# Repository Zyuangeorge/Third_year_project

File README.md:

# Third_year_project
This a python-based GUI, which is used for a battery management system project

## Hardware Requirement
1. S32K144EVB-used for serial communication

2. MC33771C BCC chip-used for battery data monitoring

3. BATT-14 emulator-used for emulating the 14 battery cells

## Software Requirement
1. Python V3.10

2. Python library

 * pyqtgraph     - data plotting

 * pandas        - data outputting

 * numpy         - data plotting

 * PySide6       - GUI building

 * PySerial        - serial communication
 
 * Plotly        - data plotting
 
## Main features
1. Serial communication with configuration of serial port

2. Real time data recording and output in .csv

3. Threshold values setting

4. Battery cell voltage displaying

5. Battery pack voltage and current displaying

6. Battery control IC temperature displaying

7. Battery and IC status displaying

8. Battery data plotting

9. CSV data opening

10. Curve zooming

11. Battery SOC and SOH information display

12. Data plotting

13. Cell balancing control

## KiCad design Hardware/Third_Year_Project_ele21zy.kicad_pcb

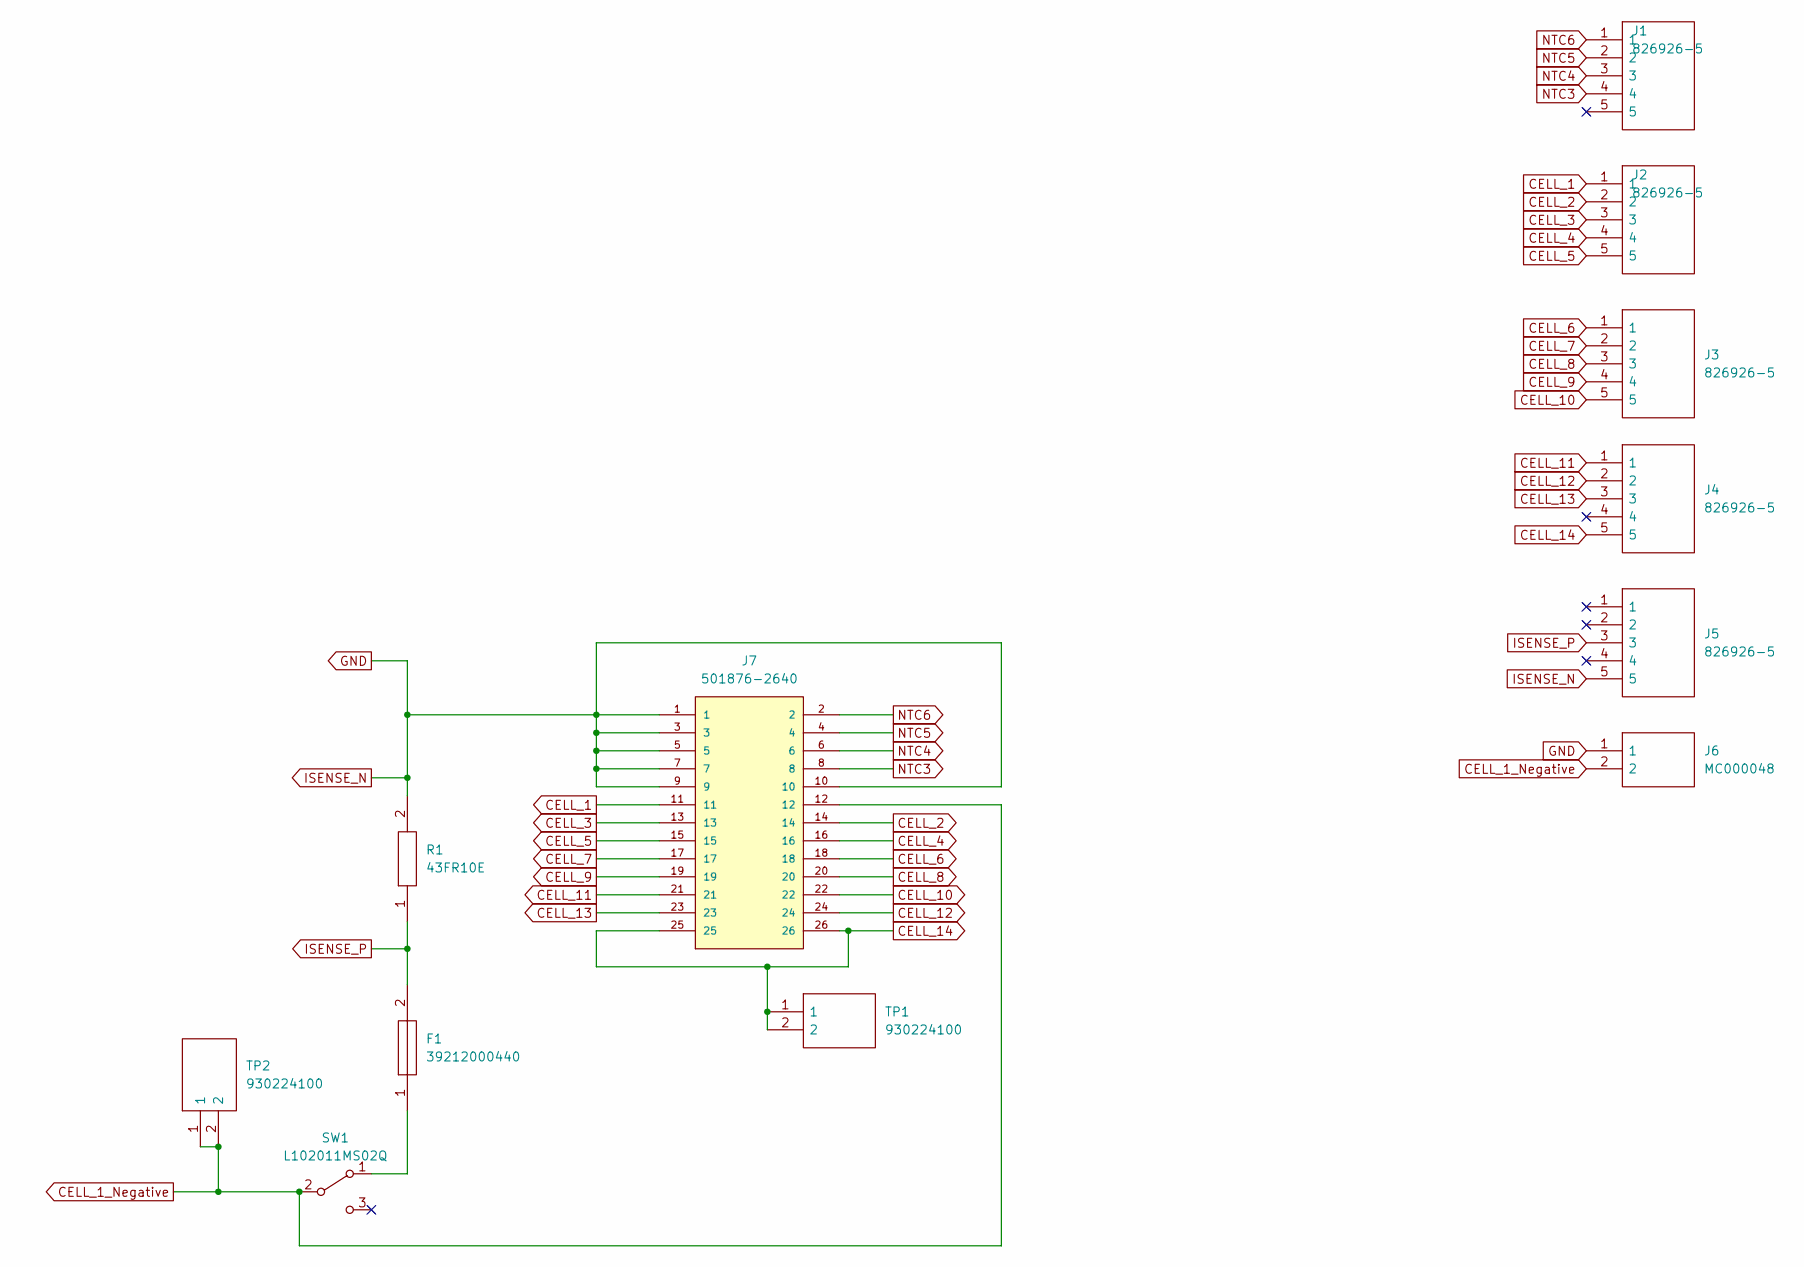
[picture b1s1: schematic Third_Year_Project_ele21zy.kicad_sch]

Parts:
F1: 39212000440; 39213150440_1; Manufacturer_Part_Number 39212000440
J1, J2, J3, J4, J5: 826926-5; RHDR5W74P0X254_1X5_1320X250X850P; Manufacturer_Part_Number 2212S-05SG-85
J6: MC000048; Manufacturer_Part_Number MC000048
J7: 501876-2640; MOLEX_501876-2640; PARTREV D
R1: 43FR10E; RESAD3750W90L1510D560; Manufacturer_Part_Number 43FR10E
SW1: L102011MS02Q
TP1, TP2: 930224100; Manufacturer_Part_Number 930224100

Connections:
CELL_1: J2.1, J7.11
CELL_1_Negative: J6.2, J7.12, SW1.2 (B), TP2.1, TP2.2
CELL_2: J2.2, J7.14
CELL_3: J2.3, J7.13
CELL_4: J2.4, J7.16
CELL_5: J2.5, J7.15
CELL_6: J3.1, J7.18
CELL_7: J3.2, J7.17
CELL_8: J3.3, J7.20
CELL_9: J3.4, J7.19
CELL_10: J3.5, J7.22
CELL_11: J4.1, J7.21
CELL_12: J4.2, J7.24
CELL_13: J4.3, J7.23
CELL_14: J4.5, J7.25, J7.26, TP1.1, TP1.2
GND: J5.5, J6.1, J7.1, J7.3, J7.5, J7.7, J7.9, J7.10, R1.2
ISENSE_P: F1.2, J5.3, R1.1
NTC3: J1.4, J7.8
NTC4: J1.3, J7.6
NTC5: J1.2, J7.4
NTC6: J1.1, J7.2
unnamed: F1.1, SW1.1 (A)

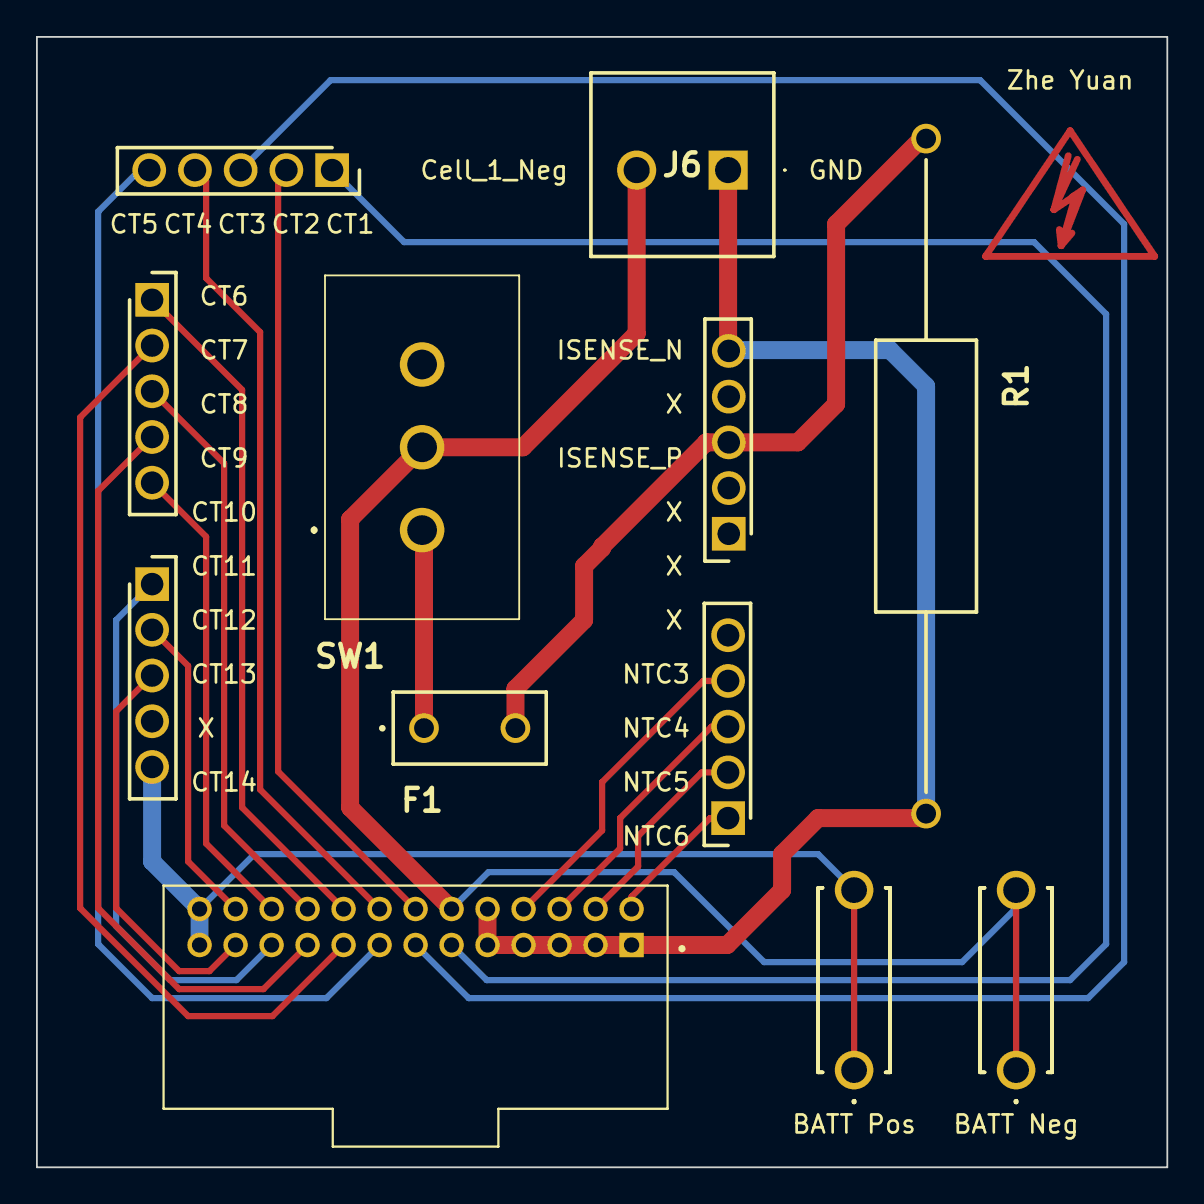
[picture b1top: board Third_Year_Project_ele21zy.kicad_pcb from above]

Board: 2 copper layers, 62.8 x 62.8 mm, 12 parts (0 on the bottom side), 22 nets.

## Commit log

2022-10-28 update GUI
2022-10-28 convert GUI to .py
2022-10-28 update UI display
2022-10-28 fix battery data display
2022-10-29 update data init
2022-10-29 update start monitor and stop monitor
2022-10-29 update util
2022-10-29 update battery status display
2022-10-29 cell status update
2022-10-29 update status button
2022-10-29 update pack status
2022-10-29 update com
2022-10-29 update receivedata
2022-10-30 update comment
2022-11-02 update UART transfer
2022-11-02 update status display
2022-11-03 update S32K codes
2022-11-06 update GUI UART transmission finished
2022-11-06 update folder structure
2022-11-06 update BMS_V1 finished
2022-11-06 update src file
2022-11-06 update version comment
2022-11-07 update GUI bugs' fixes
2022-11-07 update ui to graph button
2022-11-07 update graph demo
2022-11-07 update plot graph
2022-11-09 update graph plotting
2022-11-09 remove graph buttons
2022-11-09 update small changes
2022-11-09 update recording function(no output)
2022-11-09 update csv output
2022-11-09 update logo
2022-11-09 update small bugs
2022-11-10 update zoom graph
2022-11-10 update load data
2022-11-10 update plot window
2022-11-11 update open file
2022-11-13 update import format
2022-11-22 update current measurement
2022-11-22 update s32k code
2022-11-26 update cc method
2022-11-26 update S32K main
2022-11-28 update S32K V3 Enhanced CC
2022-11-28 update SoC and SoH (high memory)
2022-11-29 update minus value receiving
2022-11-30 Fix bugs of SoC and SoH estimation
2022-11-30 BMS GUI Version 7.3 Features: *Update automatic data output
2022-12-01 BMS GUI Version 8 Features: *Update loading data
2022-12-01 update x axis values
2022-12-01 BMS GUI Version 8.1 Features: *Update auto axis
2022-12-01 BMS GUI Version 8.2 Features: *Update EFC measurement
2022-12-01 update minus current
2022-12-02 update GUI (no focus)
2022-12-02 update exporting bugs
2022-12-02 update S32K LED, gc collect
2022-12-02 update threshold
2022-12-05 update s32K fault state
2022-12-05 Update main.c
    update threshold margin
2022-12-06 update format
2022-12-06 fix port status bug
2022-12-06 fix clear data
2022-12-06 update output directory
2022-12-10 update plotly
2022-12-10 update auto output
2022-12-11 update plotly function
2022-12-12 update OCV plot
2022-12-12 update git ignore
2022-12-12 update data
2022-12-12 update auto plotting
2022-12-12 update memory usage
2022-12-13 fix plot bugs
2022-12-13 change output time 60 to 3600
2022-12-15 update stop monitor when the port is disconnected
2022-12-15 update import plotly
2022-12-16 update OcvPlot Unit
2022-12-16 update unit test
2022-12-23 update version information and add sitation file
2022-12-23 update cff
2022-12-23 update test
2022-12-23 updata data
2022-12-30 update comment and data
2022-12-30 update data folder
2022-12-30 update version information
2023-01-12 update s32k code-variable name
2023-02-02 update data plotting
2023-02-02 remove import
2023-02-02 update settings
2023-02-02 update example
2023-02-03 update plotly dash
2023-02-03 fix bugs
2023-02-03 update battery type
2023-02-03 remove examples
2023-02-03 update data plotting function
2023-02-15 update trendline
2023-02-15 update import packages and add enum
2023-02-21 reduce memory usage
2023-02-21 internal resistance v1
2023-02-22 update error log function
2023-02-22 update log function
2023-02-22 upgrade trendline
2023-02-22 update trendline function
2023-02-23 update font size
2023-02-24 update s32k function name
2023-02-24 update balance algorithm
2023-02-24 update cell balancing (need testing)
2023-02-24 update bubble sort
2023-02-24 update balancing
2023-02-26 cell balancing function update
2023-02-26 update balancing v2
2023-02-27 update main function
2023-02-27 Cell Balancing V1
2023-02-27 update balancing GUI
2023-02-27 cell balancing v1.2 fix graph display bugs
2023-03-01 CB v1.4
2023-03-03 cb v1.5 with balance status bug
2023-03-03 cb v1.6 with close cb control problem
2023-03-03 cb v1.7 stable version
2023-03-03 Delete .vscode directory
    remove .vscode
2023-03-03 update gitignore
2023-03-03 remove pyc
2023-03-03 remove pycache folder
2023-03-04 GUI v1.1.1 require testing
2023-03-07 update hardware
2023-03-13 GUI v1.1.1 test completed, need improve output
2023-03-13 update output function, fix cb count bug
2023-03-14 fix output data bug
2023-03-14 BMS GUI Version 1.2.1
2023-03-15 update code
2023-03-15 update s32k source code
2023-03-15 update system status
2023-03-16 update load cb control data, fix clear plot bug
2023-03-16 move data and change output data to batteryType
2023-03-16 update battery type detect function, remove plotly
2023-03-16 remove open circuit current threshold
2023-03-24 bms v1.2.3
2023-03-24 update version
2023-03-25 update test codes
2023-03-26 update cb control plot function
2023-03-26 improve data plotting
2023-03-26 update combine plot legend
2023-03-27 update accurate soc data
2023-03-27 update balancing soc plot
2023-03-27 update soc plot legend
2023-03-27 update combined plot
2023-03-27 update charging LA battery data
2023-03-27 update 27th Data
2023-03-28 update plotly graph style
2023-04-02 update codes
2023-04-03 fix trendline bug andupdateinternal resistancedata
2023-04-03 update graph download config
2023-04-03 update download config
2023-04-12 update 7cells
2023-04-12 change init number
2023-04-12 update s32k stable 7 cell
2023-04-20 update plot
2023-04-24 update data analysis plot
2023-04-28 update SoH method sselection
